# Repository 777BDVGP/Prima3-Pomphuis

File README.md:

# Prima3 Pomphuis — pump house & irrigation controller

A pump house controller on a **WEMOS LOLIN S3 Mini** (ESP32-S3): it fills a water
tank from a borehole, runs up to **9 irrigation zones** through **7 solenoid
valves**, drives a tank filter pump, and keeps track of two households that share
one borehole. Everything is a web page on your own WiFi — no cloud, no app.

**Install / update page:** https://777bdvgp.github.io/Prima3-Pomphuis/

**Contents:** [Features](#features) · [Hardware](#hardware) · [Pin map](#pin-map) ·
[Installing the firmware](#installing-the-firmware) · [First start: WiFi](#first-start-wifi) ·
[Using the rain gauge](#using-the-rain-gauge) · [Updating](#updating) · [Building the firmware yourself](#building-the-firmware-yourself) ·
[Licence](#licence)

> **Who this is for:** someone with hands-on experience in electronics and
> irrigation plumbing. It is not a kit manual. The guide grows over time —
> parts marked **(to be completed)** get more detail and photos later.

## Features

- **HOME** — live status: tank level, float switches, filter pressure, borehole
  pump, which household is pumping, active irrigation zone, manual start / stop.
- **Irrigation** — 9 zones, each with its own valve configuration, start date /
  time, duration, every-N-days frequency, water source (tank or borehole),
  per-weekday suspend, manual or scheduled mode. A 7-day suspend calendar
  switches off all irrigation on chosen days.
- **Rain gauge** (optional) — asks a [Rain Gauge](https://777bdvgp.github.io/RainGauge/)
  on the same network every hour whether to irrigate today; zones with
  **Respect Rain Gauge Recommendation = Yes** are skipped when it says no.
  See [Using the rain gauge](#using-the-rain-gauge).
- **Tank** — fill by float switch or level sensor, any time or only inside a
  time window, start / stop levels, borehole timeout and retry, filter pump
  delay after filling, filter backwash warning from a pressure sensor.
- **Valves** — names for the 7 valves and 9 configurations (which valves are open
  for which zone / tank fill / default). A valve test page (system disabled only).
- **NTFY** — free push alerts on your phone ([ntfy.sh](https://ntfy.sh)): filter
  backwash, borehole pumping, per household.
- **Reports** — general, irrigation, water used and filter logs (last 200 lines each).
  The irrigation log has a line when a zone **starts**, when it **ends** (with the
  duration) and when a run is **skipped**, with the reason (rain gauge, suspended).
- **Remote pump API** — `/pumpstart`, `/pumpstop`, `/pumpstatus` (60 s heartbeat)
  so another controller can start the borehole pump.
- **WiFi** — saved networks list (add / delete, passwords never shown), joins the
  strongest network in range and the **strongest access point** when several
  share one WiFi name (mesh / multi-AP). Setup hotspot **Prima3-Setup** for a new
  board or when no network can be reached.
- **ABOUT** — **firmware update from GitHub** (CHECK / INSTALL) or from an uploaded `.bin`.
- **Safety** — software watchdog, gateway ping (reboots after 5 min without the
  router), reboot when WiFi is lost for 60 s, nightly reboot at 00:13, heap guard.

## Hardware

- WEMOS LOLIN S3 Mini (ESP32-S3, 4 MB flash, 2 MB PSRAM). The PCB was designed for
  the S2 Mini; the S3 Mini is a pin-compatible drop-in.
- PCB: Eagle files in [`PCB/`](PCB) (`WEMOS_ESP32_2S_V4_for_S3.sch` / `.brd`).
  Gerbers **(to be completed)**.
- Relay / driver outputs for 7 solenoid valves, the borehole pump (active high),
  filter pump relay and status LEDs; inputs for float switches, buttons, the two
  "household pumping" detectors and the tank level / filter pressure sensors.
- Bill of materials, wiring and photos **(to be completed)**.

## Pin map

| Output | GPIO | | Input | GPIO |
|---|---|---|---|---|
| Solenoid valve 03 | 4 | | Tank filter pressure (ADC) | 1 |
| Solenoid valve 08 | 6 | | Tank level sensor (ADC) | 3 |
| Solenoid valve 10 | 12 | | System enable / disable button | 35 |
| Solenoid valve 07 | 7 | | Household 2 pumping | 34 |
| Solenoid valve 02 | 13 | | Household 1 pumping | 36 |
| Solenoid valve 09 | 8 | | Tank full float switch | 38 |
| Solenoid valve 17 | 11 | | Tank low float switch | 44 |
| Borehole pump (HIGH = run) | 2 | | Manual borehole start / stop | 37 |
| Filter pump relay | 21 | | Filter pump on / off button | 43 |
| Manual pump LED | 10 | | BOOT button (WiFi setup) | 0 |
| Household 2 pumping LED | 9 | | | |
| Household 1 pumping LED | 14 | | | |
| Tank float high LED | 16 | | | |
| Tank float low LED | 18 | | | |
| System disabled LED | 17 | | | |
| Extra output 1 / 2 | 33 / 5 | | | |

GPIO 43 / 44 are the S3's UART0 pins — used as inputs here, so there is no serial
log on UART0 (the USB port carries `Serial`).

## Installing the firmware

No PlatformIO needed: open **https://777bdvgp.github.io/Prima3-Pomphuis/** in
Chrome or Edge on a PC, plug the S3 Mini in with a USB **data** cable and press
**CONNECT**. Choose **Erase** for a new board, then **Install**. If no port shows
up, hold **BOOT (0)**, tap **RST**, release **BOOT** and try again.

## First start: WiFi

1. A new controller opens its own hotspot **Prima3-Setup** (the LED blinks red fast).
2. Connect a phone to it — the setup page opens by itself (otherwise browse to `http://192.168.4.1/`).
3. Pick your network, type the password and give it a **fixed IP** (other devices
   such as a remote pump controller reach it by IP), press **SAVE & RESTART**.
4. Put the phone back on your WiFi and open the fixed IP (or `http://primapomphuis.local/`).

More networks: **SETTINGS → WiFi Networks**. Hold **BOOT** while powering up to open
the setup hotspot again. If no saved network can be reached for about 4 minutes,
the hotspot opens by itself for 5 minutes, then the controller restarts and tries again.

## Using the rain gauge

Optional: a [Rain Gauge](https://777bdvgp.github.io/RainGauge/) on the same network
decides whether the garden needs water today.

1. **SETTINGS** — tick **Use Rain Gauge** and enter its IP as **Rain Gauge IP**
   (e.g. `192.168.1.50`). The controller asks the gauge at once and then every hour.
2. **IRRIGATION** — for every zone that must follow the gauge, set
   **Respect Rain Gauge Recommendation = Yes**. A zone set to **No** waters on its
   schedule whatever the gauge says.

SETTINGS shows the gauge's last answer and an **Irrigation Today** badge:

| Badge | Meaning |
|---|---|
| green **IRRIGATE** | the gauge says water (or Use Rain Gauge is off) |
| red **NO IRRIGATION TODAY** | the gauge says skip; zones with the setting on Yes are skipped |
| orange **SKIP - but no zone has Respect Rain Gauge Recommendation = Yes** | the gauge says skip, but no zone listens to it, so they all water |

A skipped run is written to the irrigation log, e.g.
`Skipped: FRONT - rain gauge: Skip - soil still has water …`, and the zone moves on
to its next date.

**If the gauge cannot be reached** (no power, WiFi down, wrong IP) the controller
keeps its last answer for 3 hours, then waters as normal — and after a restart (every
night at 00:13) it waters as normal at once — so a broken gauge never leaves the
garden dry for more than a day. The general log says "Rain gauge not reachable" and
"Rain gauge reachable again". If the rain gauge itself is set to *No Irrigation*
(plain rain meter) it always answers "irrigate".

## Updating

On the **ABOUT** page: **CHECK FOR UPDATE** compares the version with the one on the
install page; **INSTALL FROM GITHUB** downloads and installs it (not while a zone
irrigates or the borehole pump runs). Settings and logs are kept; a failed
download leaves the old firmware running. Without internet at the controller:
download [`prima3.bin`](docs/firmware/prima3.bin) and use **UPLOAD & INSTALL**.

## Building the firmware yourself

[PlatformIO](https://platformio.org/) project in [`Prima3/`](Prima3):

```bash
cd Prima3
pio run -e usb -t upload                                   # first flash over USB
pio run -e ota -t upload --upload-port <controller ip>     # later over WiFi
```

Optional built-in WiFi networks: copy `src/wifi_secrets.example.h` to
`src/wifi_secrets.h` (git-ignored). Builds with that file are named `_PRIVATE` —
do not share them, your passwords are inside.

## Licence

[CC BY-NC 4.0](LICENSE) — free for personal use, not for sale. No warranty: this
controls pumps and valves, and the pumps run on mains power — have mains wiring
done or checked by a qualified person.

Copyright (c) 2026 Bennie Vermeulen

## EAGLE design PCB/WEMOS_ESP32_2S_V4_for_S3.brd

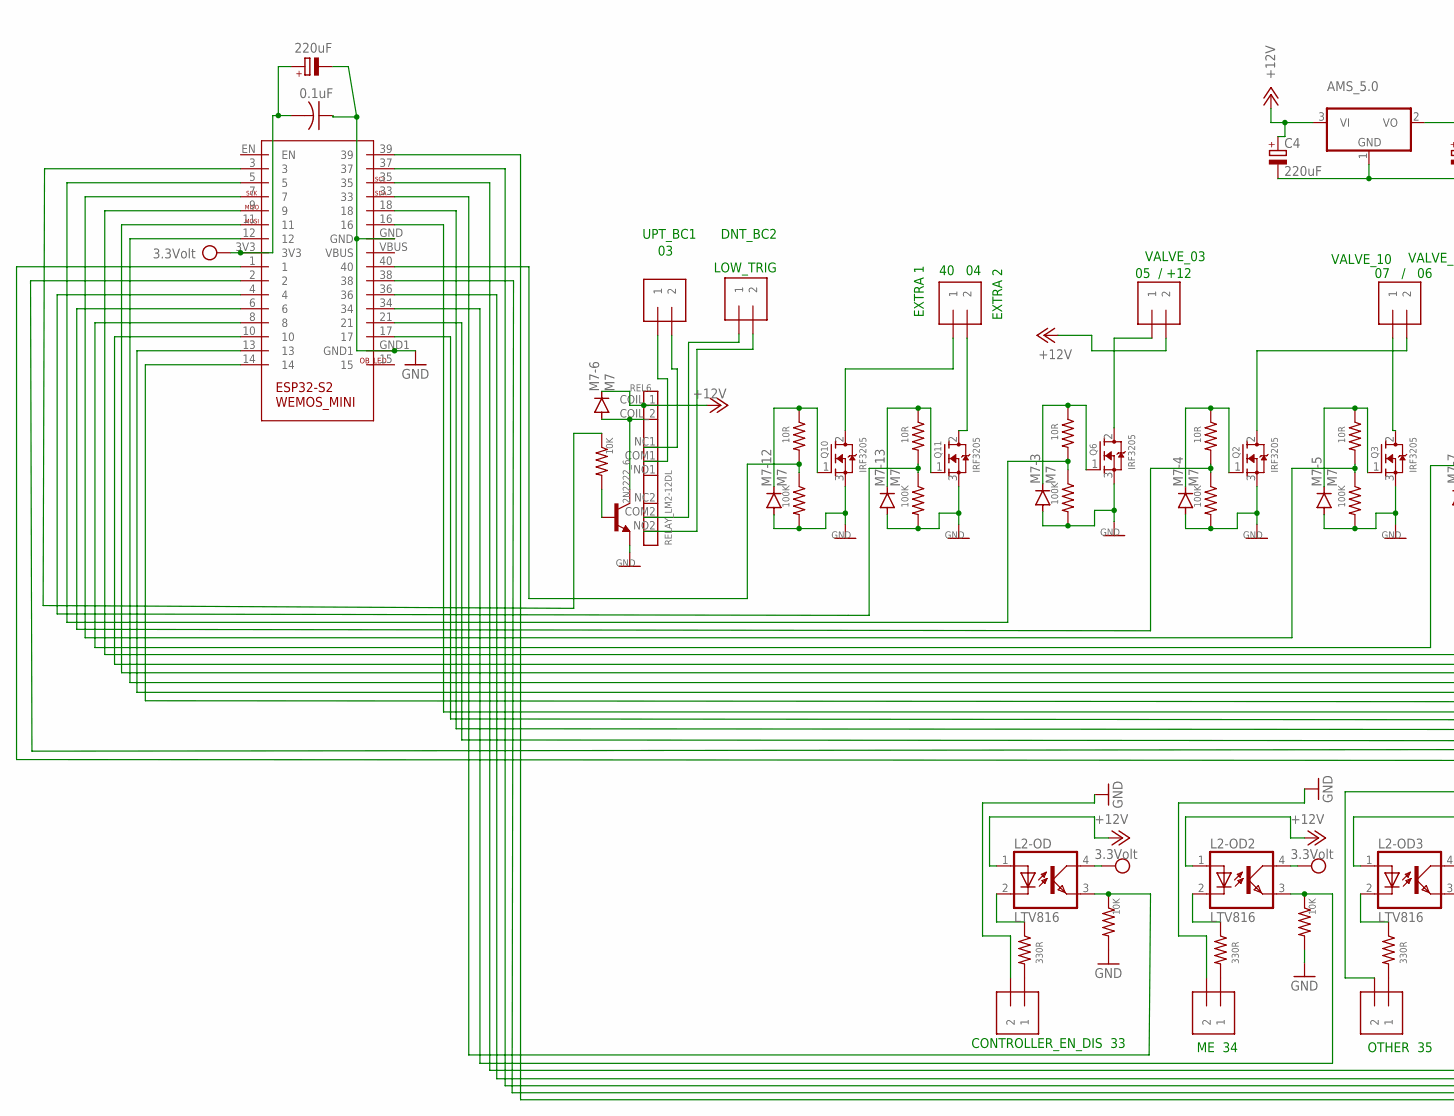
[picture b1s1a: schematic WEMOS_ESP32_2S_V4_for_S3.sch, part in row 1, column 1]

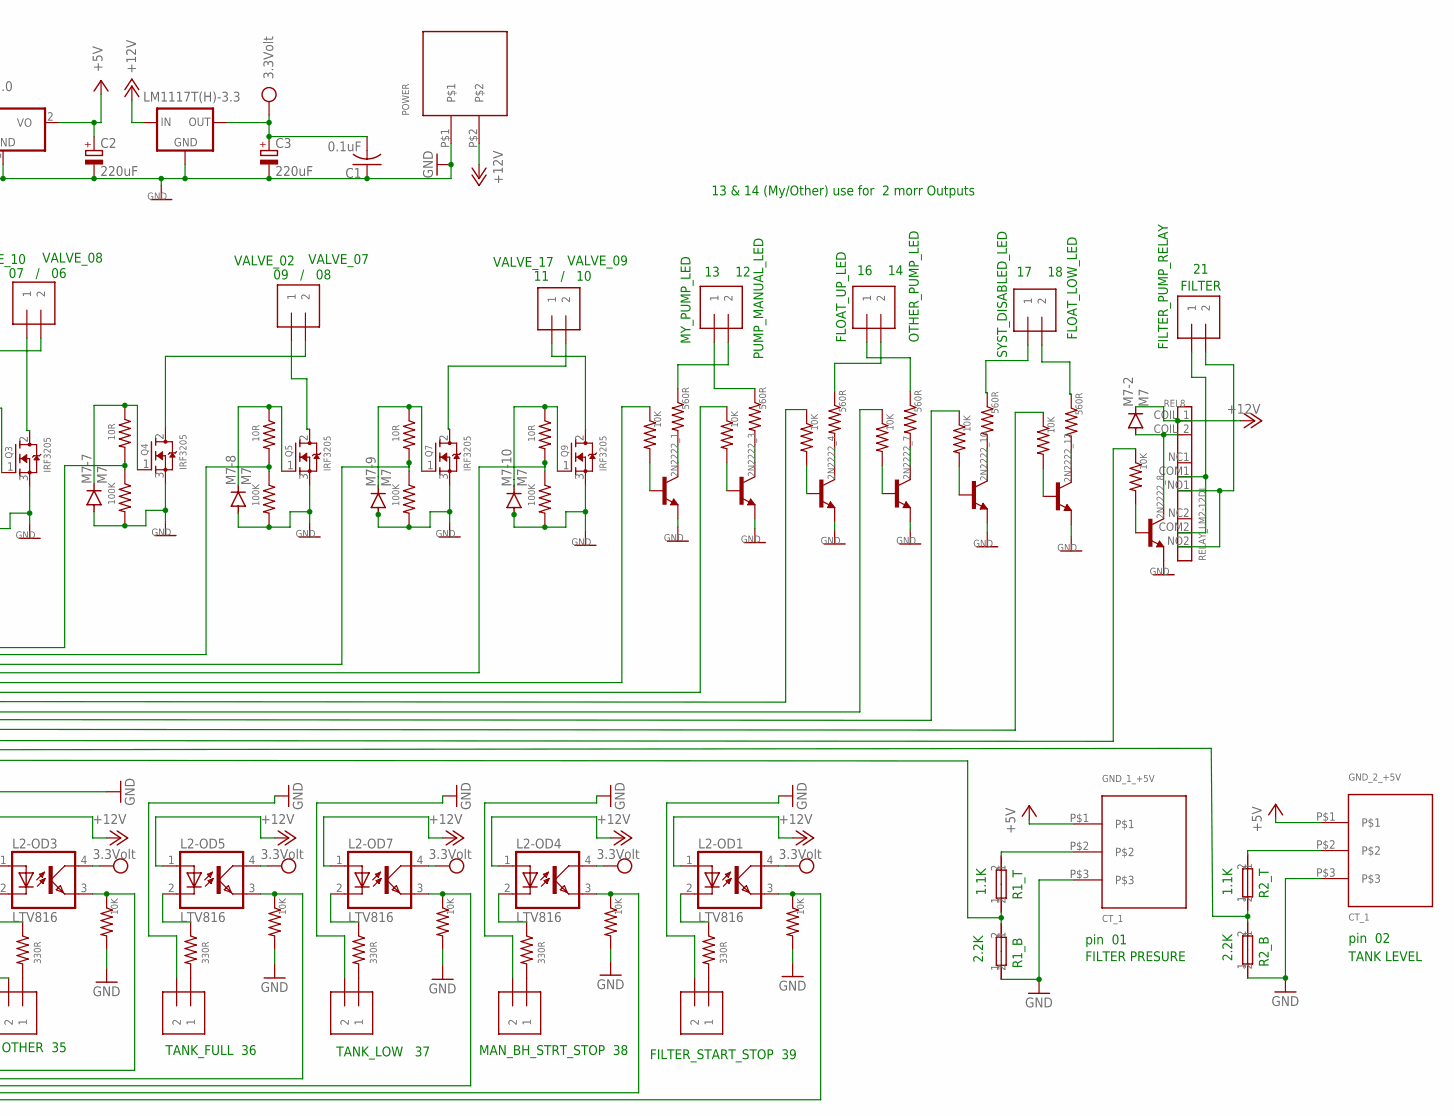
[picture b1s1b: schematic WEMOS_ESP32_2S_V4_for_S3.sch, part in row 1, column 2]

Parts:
2N2222_1, 2N2222_3, 2N2222_4, 2N2222_6, 2N2222_7, 2N2222_8, 2N2222_10, 2N2222_12: 2N3904; TO92
06__07, 08__09, 10__11, 12__13, 14__16, 18__17, 40__04: FLOAT; 1X2-3.5MM
+12V_05: FLOAT; 1X2-3.5MM
+_33: AAA; 1X2-3.5MM
+_34, +_35, +_36, +_37, +_38, +_39: TERMINNAL-3.5MM-2-3.5MMDOUBLE; 1X2-3.5MM
AMS_5.0: AMS1117DB; SOT223
C1, C5: 0.1uF; C050-025X075
C2, C3, C4, C6: 220uF; E2,5-7
DNT_03: FLOAT; 1X2-3.5MM
FIL__21: FILTER; 1X2-3.5MM
GND_1_+5V, GND_2_+5V: CT_1; 1X3-3.5MM_TERM
IC1: LM1117T(H)-3.3; TO220H
L2-OD, L2-OD1, L2-OD2, L2-OD3, L2-OD4, L2-OD5, L2-OD7: LTV816; DIL04
M7-2, M7-3, M7-4, M7-5, M7-6, M7-7, M7-8, M7-9, M7-10, M7-12, M7-13: M7; SOD106-R
POWER: TERMINAL-5.08MM-2BIG_HOLE; TERM-5.05-2_BH
Q2, Q3, Q4, Q5, Q6, Q7, Q9, Q10, Q11: IRF3205; TO220V
R1, R7, R10, R13, R15, R17, R19, R23, R24, R30, R34, R36, R40, R44, R48: 10K; R0805
R1_B: 2.2K; 0207/10
R1_B1: 2.2k; 0207/10
R1_T, R2_T1: 1.1K; 0207/10
R2, R6, R9, R20, R26, R28, R32, R46, R50: 100K; R0805
R3, R12, R14, R16, R18, R22, R29: 330R; R0805
R4, R35, R37, R41, R45, R49: 560R; R0805
R5, R8, R11, R25, R27, R31, R38, R43, R47: 10R; R0805
REL6, REL8: RELAY_LM2-12DL; RELAY4078
U$1: WEMOS_S2_MINI
UPT_03: FLOAT; 1X2-3.5MM

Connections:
+5V: AMS_5.0.2 (VO), C2.+, GND_1_+5V.P$1, GND_2_+5V.P$1
+12V: +12V_05.2, AMS_5.0.3 (VI), C4.+, IC1.3 (IN), L2-OD.1 (A), L2-OD1.1 (A), L2-OD2.1 (A), L2-OD3.1 (A), L2-OD4.1 (A), L2-OD5.1 (A), L2-OD7.1 (A), M7-2.C, M7-6.C, POWER.P$2, REL6.COIL_1 (COIL1), REL8.COIL_1 (COIL1)
GND: 2N2222_1.3 (E), 2N2222_3.3 (E), 2N2222_4.3 (E), 2N2222_6.3 (E), 2N2222_7.3 (E), 2N2222_8.3 (E), 2N2222_10.3 (E), 2N2222_12.3 (E), +_33.2, +_34.2, +_35.2, +_36.2, +_37.2, +_38.2, +_39.2, AMS_5.0.1 (GND), C1.1, C2.-, C3.-, C4.-, C5.1, C6.-, GND_1_+5V.P$3, GND_2_+5V.P$3, IC1.1 (GND), M7-3.A, M7-4.A, M7-5.A, M7-7.A, M7-8.A, M7-9.A, M7-10.A, M7-12.A, M7-13.A, POWER.P$1, Q2.3 (S), Q3.3 (S), Q4.3 (S), Q5.3 (S), Q6.3 (S), Q7.3 (S), Q9.3 (S), Q10.3 (S), Q11.3 (S), R1_B.1, R1_B1.1, R2.2, R6.2, R7.2, R9.2, R13.2, R15.2, R17.2, R19.2, R20.2, R23.2, R26.2, R28.2, R30.2, R32.2, R46.2, R50.2, U$1.GND, U$1.GND1
unnamed: 08__09.1, Q5.2 (D)
unnamed: 2N2222_6.2 (B), R10.2
unnamed: REL6.COM1, UPT_03.1
unnamed: R47.2, R50.1, U$1.4
unnamed: L2-OD.2 (C), R3.1
unnamed: R43.2, R46.1, U$1.40
unnamed: M7-3.C, Q6.1 (G), R38.1
unnamed: R2.1, R38.2, U$1.5
unnamed: 10__11.2, Q7.2 (D)
unnamed: R1_B1.2, R2_T1.1, U$1.2
unnamed: 2N2222_8.2 (B), R24.2
unnamed: 40__04.2, Q11.2 (D)
unnamed: 06__07.2, Q2.2 (D)
unnamed: 2N2222_1.1 (C), R4.2
unnamed: 06__07.1, Q3.2 (D)
unnamed: M7-7.C, Q4.1 (G), R11.1
unnamed: R10.1, U$1.3
unnamed: R11.2, R20.1, U$1.8
unnamed: 08__09.2, Q4.2 (D)
unnamed: L2-OD1.2 (C), R29.1
unnamed: +_39.1, R29.2
unnamed: +12V_05.1, Q6.2 (D)
unnamed: M7-4.C, Q2.1 (G), R5.1
unnamed: R5.2, R6.1, U$1.6
unnamed: R1.1, U$1.12
unnamed: M7-5.C, Q3.1 (G), R8.1
unnamed: R8.2, R9.1, U$1.7
unnamed: +_33.1, R3.2
unnamed: M7-8.C, Q5.1 (G), R25.1
unnamed: R25.2, R26.1, U$1.9
unnamed: 2N2222_1.2 (B), R1.2
unnamed: M7-9.C, Q7.1 (G), R27.1
unnamed: R27.2, R28.1, U$1.10
unnamed: 12__13.2, R4.1
unnamed: L2-OD7.3 (EMIT), R23.1, U$1.37
unnamed: 12__13.1, R35.1
unnamed: 14__16.2, R37.1
unnamed: 10__11.1, Q9.2 (D)
unnamed: M7-10.C, Q9.1 (G), R31.1
unnamed: R31.2, R32.1, U$1.11
unnamed: L2-OD2.3 (EMIT), R13.1, U$1.34
unnamed: L2-OD.3 (EMIT), R7.1, U$1.33
unnamed: R34.1, U$1.13
unnamed: 2N2222_3.2 (B), R34.2
unnamed: 2N2222_3.1 (C), R35.2
unnamed: L2-OD1.3 (EMIT), R30.1, U$1.39
unnamed: L2-OD2.2 (C), R12.1
unnamed: R36.1, U$1.14
unnamed: R1_B.2, R1_T.1, U$1.1
unnamed: 2N2222_4.2 (B), R36.2
unnamed: 2N2222_4.1 (C), R37.2
unnamed: 14__16.1, R41.1
unnamed: 18__17.1, R45.1
unnamed: 18__17.2, R49.1
unnamed: +_34.1, R12.2
unnamed: L2-OD5.3 (EMIT), R19.1, U$1.36
unnamed: GND_1_+5V.P$2, R1_T.2
unnamed: L2-OD3.2 (C), R14.1
unnamed: GND_2_+5V.P$2, R2_T1.2
unnamed: +_35.1, R14.2
unnamed: L2-OD3.3 (EMIT), R15.1, U$1.35
unnamed: 2N2222_6.1 (C), M7-6.A, REL6.COIL_2 (COIL2)
unnamed: DNT_03.2, REL6.NO2
unnamed: R40.1, U$1.16
unnamed: REL6.NC1, UPT_03.2
unnamed: 2N2222_7.2 (B), R40.2
unnamed: 2N2222_7.1 (C), R41.2
unnamed: DNT_03.1, REL6.COM2
unnamed: L2-OD4.2 (C), R16.1
unnamed: 40__04.1, Q10.2 (D)
unnamed: +_38.1, R16.2
unnamed: L2-OD4.3 (EMIT), R17.1, U$1.38
unnamed: L2-OD5.2 (C), R18.1
unnamed: +_36.1, R18.2
unnamed: M7-12.C, Q10.1 (G), R43.1
unnamed: R44.1, U$1.17
unnamed: 2N2222_10.2 (B), R44.2
unnamed: 2N2222_10.1 (C), R45.2
unnamed: M7-13.C, Q11.1 (G), R47.1
unnamed: L2-OD7.2 (C), R22.1
unnamed: +_37.1, R22.2
unnamed: R48.1, U$1.18
unnamed: 2N2222_12.2 (B), R48.2
unnamed: 2N2222_12.1 (C), R49.2
unnamed: 2N2222_8.1 (C), M7-2.A, REL8.COIL_2 (COIL2)
unnamed: FIL__21.2, REL8.NO1, REL8.NO2
unnamed: FIL__21.1, REL8.COM1, REL8.COM2
unnamed: R24.1, U$1.21
VCC: C1.2, C3.+, C5.2, C6.+, IC1.2 (OUT), L2-OD.4 (COL), L2-OD1.4 (COL), L2-OD2.4 (COL), L2-OD3.4 (COL), L2-OD4.4 (COL), L2-OD5.4 (COL), L2-OD7.4 (COL), U$1.3V3

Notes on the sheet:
LOW_TRIG
05 / +12
07 / 06
09 / 08
11 / 10
FILTER
R1_T
R1_B
R2_T
R2_B
VALVE_03
VALVE_10
VALVE_08
VALVE_02
VALVE_07
VALVE_17
VALVE_09
UPT_BC1
DNT_BC2
MY_PUMP_LED
PUMP_MANUAL_LED
FLOAT_UP_LED
OTHER_PUMP_LED
SYST_DISABLED_LED
FLOAT_LOW_LED
FILTER_PUMP_RELAY
CONTROLLER_EN_DIS 33
ME 34
OTHER 35
TANK_FULL 36
TANK_LOW 37
MAN_BH_STRT_STOP 38
FILTER_START_STOP 39
pin 01
pin 02
FILTER PRESURE
TANK LEVEL
1.1K
2.2K
EXTRA 2

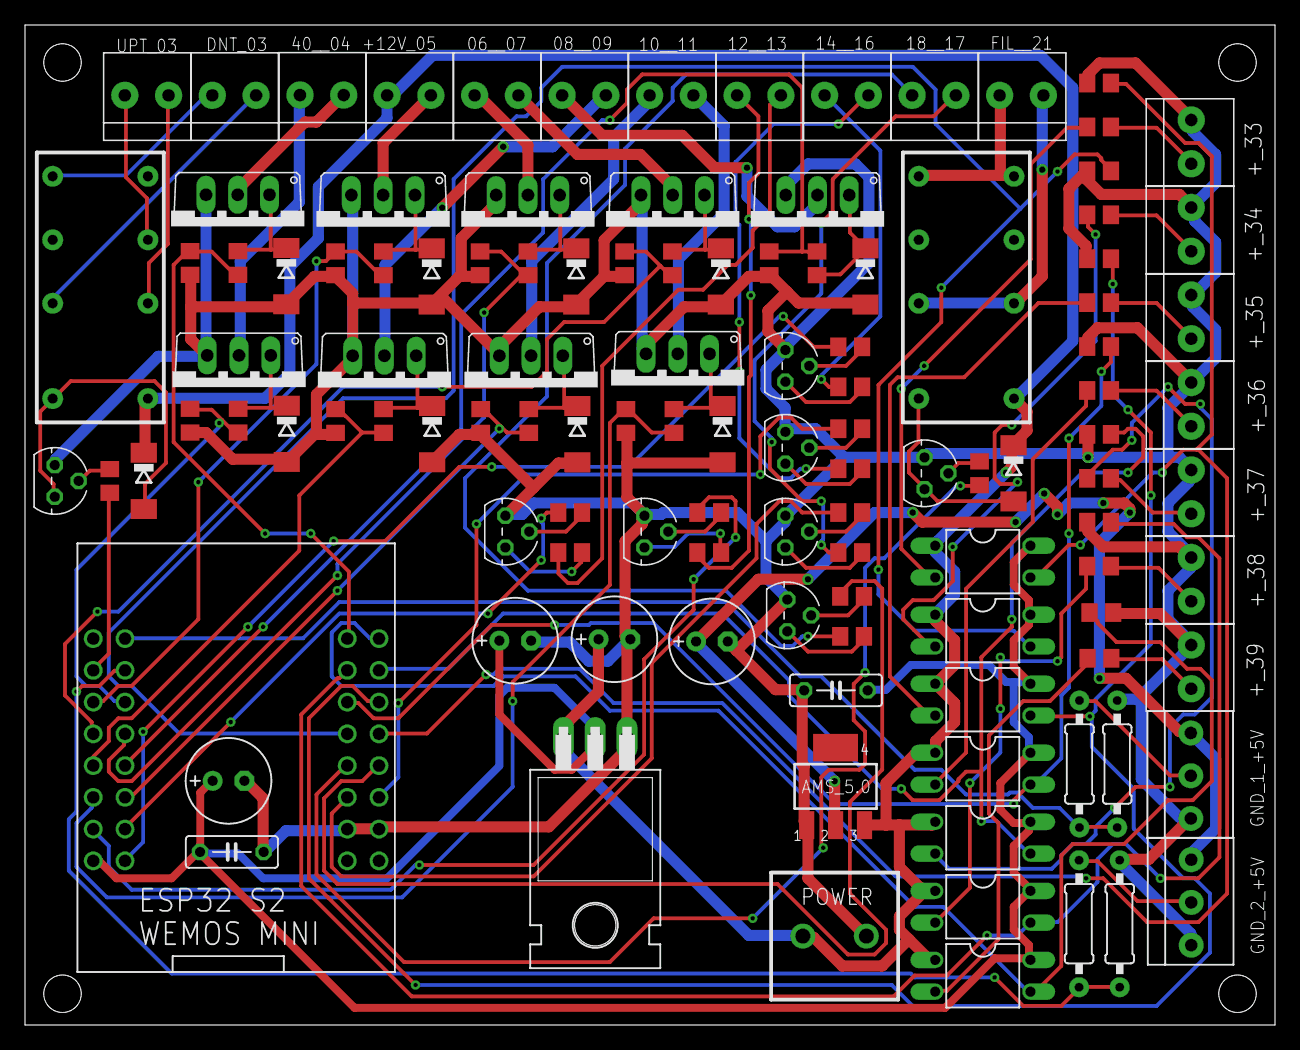
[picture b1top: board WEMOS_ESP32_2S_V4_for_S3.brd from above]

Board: 2 copper layers, 100.0 x 80.0 mm, 117 parts (0 on the bottom side), 92 nets.
